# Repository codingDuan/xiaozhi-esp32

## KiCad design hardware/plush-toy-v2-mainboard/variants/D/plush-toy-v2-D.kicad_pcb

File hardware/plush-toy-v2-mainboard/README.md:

# 毛绒玩具主板二期

设计方案：[`docs/superpowers/specs/2026-10-05-plush-toy-v2-hardware-design.md`](../../docs/superpowers/specs/2026-10-05-plush-toy-v2-hardware-design.md)
实施计划：[`docs/superpowers/plans/2026-10-05-plush-toy-v2-hardware.md`](../../docs/superpowers/plans/2026-10-05-plush-toy-v2-hardware.md)
选型记录：[`SELECTION.md`](SELECTION.md)　电池防反接：[`BATTERY_PROTECTION.md`](BATTERY_PROTECTION.md)

四个版本共用一份电路描述（`scripts/v2/`），各自一份布局（`scripts/placement_<X>.py`），产物在 `variants/<X>/`。

## 命令

```sh
cd hardware/plush-toy-v2-mainboard/scripts
KP=/Applications/KiCad/KiCad.app/Contents/Frameworks/Python.framework/Versions/Current/bin/python3
python3 -m unittest test_parts_db test_gpio test_core test_variants test_netlist   # 电路描述与原理图
python3 gen_schematic.py --variant A
$KP gen_pcb.py --variant A
$KP -m unittest test_pcb_A
$KP shrink.py --variant A        # 试探能否继续缩小（不改文件）
$KP fanout.py --variant A && $KP route.py --variant A   # 扇出 + Freerouting，成功后存 build/routed-snapshot
$KP post_route.py --variant A --from-snapshot           # 网格补线（不重跑 Freerouting）
bash export_fab.sh A             # 测试 + Gerber/BOM/坐标/库存报告/渲染图 → variants/A/fab/
python3 export_wiring.py --variant A                    # 接线表与外购清单
$KP export_camera_check.py --variant C                  # C/D：1:1 摄像头实物核验稿（非生产文件）
```

## 版本状态

| 版本 | 状态 | 尺寸 |
|---|---|---|
| A 不带摄像头 · 单面 | 生产文件已出，待委托方决定是否打样 | 54×46mm |
| B 不带摄像头 · 双面 | 生产文件已出，待首板实测 | 50×46mm |
| C 带摄像头 · 单面 | 生产文件已出，待首板断电测量与实测 | 65×55mm |
| D 带摄像头 · 双面 | 生产文件已出，待首板断电测量与实测 | 65×55mm |

## 版本 A 尺寸迭代

| 轮次 | 尺寸 | 面积 / 一期 5400mm² | 结果 |
|---|---|---|---|
| 0 | 52×42 | 40% | spec 估算起点。按委托方要求加每个引脚的丝印标注后，右下角、右上角的标注与座子冲突 |
| 1 | 52×46 | 44% | 可行：全部器件与丝印放下，布局测试通过 |
| 2 | 51×46 | 43% | 失败：左上安装孔与触摸座重叠 |
| 2 | 52×45 | 43% | 失败：触摸座、测温座的引脚标注放不下 |
| 4 | 54×46 | 46% | 去耦复查后加宽 2mm（委托方 2026-10-05 同意）：去耦电容须贴引脚同侧，52×46 只剩 1 个降压位置且布不通 |

**结论**：单面版本的尺寸由板边长度决定，不由面积决定：上边 4 个、下边 4 个、右边 3 个出线座已排满，左边是模组与天线。再缩小需要减少出线座或改双面（版本 B）。
暂不加布线余量：板中部仍有空地，Task 10 布线不收敛时再加。

## 版本 A 结果（2026-10-05）

| 项 | 结果 |
|---|---|
| 尺寸 | 54×46mm，4 层，面积 2484mm²，**一期的 46%** |
| 器件 | 88 颗全部贴片（单面），BOM 38 行；另有 8 个背面测试点、2 个安装孔，**板上无手焊件** |
| 扩展库 | 20 种（每种每单一笔换料费），库存全部 ≥ 20，见 `variants/A/fab/parts_report.txt` |
| 单板器件费 | 约 $13.1（嘉立创 1–49 片档；ESP32 模组 $5.14 占四成，其次 MAX98357A $1.32、LIS2DH12 $0.93、eFuse $0.87） |
| DRC（重新灌铜后） | 0 错误、0 未连接、原理图一致性 0；孔距按错误检查。警告 17 条均为丝印：舵机排针外形伸出板边（设计如此）、模组天线外形、外框相碰、电池座自带外框压到其固定焊盘（导出时自动裁掉） |
| 布局质量（测试保证） | 去耦电容焊盘距所服务引脚 ≤ 3mm 且在同侧（第二颗储能电容 ≤ 6mm）；降压热回路表层 1.2mm；降压输出焊盘直接打孔进 3V3 平面；功率网络无长细线；出线座全部卧式、开口朝板边；功能名不会印到邻座旁 |
| 生产文件 | `variants/A/fab/`：`gerber.zip`、`bom.csv`、`positions.csv` |
| 接线 / 验收 | [`variants/A/WIRING.md`](variants/A/WIRING.md)、[`variants/A/TESTING.md`](variants/A/TESTING.md) |
| 渲染图 | `variants/A/renders/final_top.png`、`final_bottom.png` |

固件需要配套改动（另立计划）：I2C 在 GPIO43/44，LIS2DH12 地址 0x19，开机后经 I2C 关掉 IP5306 轻载关机，
按 CC 电压判定是否允许加热。

## 版本 C 结果（2026-10-05）

| 项 | 结果 |
|---|---|
| 尺寸 | 65×55mm，4 层，单面贴片 |
| 装配 | 除背面测试点和安装孔外，所有器件均为正面 SMT；所有线束座为卧式、开口朝板外，板上无手焊件 |
| 静态验收 | `test_pcb_C` 24/24，`test_drc_C` 5/5；重新灌铜后 0 DRC 错误、0 未连接、0 原理图一致性问题 |
| 摄像头安全 | J_CAM 自动检查焊盘反序映射；实物照片与一期 2 号板断电导通记录交叉确认：触点朝下、镜头朝板外、摄像头 pin 1 → PCB pad 24；首板上电前仍须通过 spec §7.4 断电测量 |
| 生产文件 | `variants/C/fab/`：`gerber.zip`、44 行 `bom.csv`、Top 107 项 `positions.csv`、库存报告；全部料号库存 ≥20 |
| 接线 / 验收 | [`variants/C/WIRING.md`](variants/C/WIRING.md)、[`variants/C/TESTING.md`](variants/C/TESTING.md)、[`variants/C/CAMERA_VERIFICATION.md`](variants/C/CAMERA_VERIFICATION.md) |
| 渲染图 | `variants/C/renders/final_top.png`、`final_bottom.png` |

## 版本 D 结果（2026-10-05）

| 项 | 结果 |
|---|---|
| 尺寸 | 65×55mm，4 层，双面贴片 |
| 装配 | 107 个工厂贴装坐标：Top 19 + Bottom 88；所有线束座为卧式、开口朝板外，板上无手焊件 |
| 静态验收 | `test_pcb_D` 26/26，`test_drc_D` 6/6；重新灌铜后 0 DRC 错误、0 未连接、0 原理图一致性问题 |
| 摄像头安全 | 与 C 相同的反序映射和实物方向证据；首板上电前仍须通过 spec §7.4 断电测量 |
| 生产文件 | `variants/D/fab/`：`gerber.zip`（含 `F.Paste`、`B.Paste`）、44 行 `bom.csv`、Top 19 + Bottom 88 项 `positions.csv`、库存报告；全部料号库存 ≥20 |
| 接线 / 验收 | [`variants/D/WIRING.md`](variants/D/WIRING.md)、[`variants/D/TESTING.md`](variants/D/TESTING.md)、[`variants/D/CAMERA_VERIFICATION.md`](variants/D/CAMERA_VERIFICATION.md) |
| 渲染图 | `variants/D/renders/final_top.png`、`final_bottom.png` |

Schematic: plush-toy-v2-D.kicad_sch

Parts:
C_ADC: 100nF; C_0402_1005Metric; LCSC C1525
C_AMP: 100nF; C_0402_1005Metric; LCSC C1525
C_AMP_BULK: 10uF; C_0603_1608Metric; LCSC C19702
C_BAT_NTC: 100nF; C_0402_1005Metric; LCSC C1525
C_BUCK_HF: 100nF; C_0402_1005Metric; LCSC C1525
C_BUCK_IN: 10uF; C_0603_1608Metric; LCSC C19702
C_BUCK_OUT1, C_BUCK_OUT2: 22uF; C_0805_2012Metric; LCSC C45783
C_CAM_AVDD: 100nF; C_0402_1005Metric; LCSC C1525
C_CAM_DVDD: 100nF; C_0402_1005Metric; LCSC C1525
C_CAM_RST: 100nF; C_0402_1005Metric; LCSC C1525
C_CC_SENSE: 10nF; C_0402_1005Metric; LCSC C15195
C_CHG_BAT: 22uF; C_0805_2012Metric; LCSC C45783
C_CHG_VIN: 22uF; C_0805_2012Metric; LCSC C45783
C_EFUSE_DVDT: 3.3nF; C_0402_1005Metric; LCSC C696855
C_EFUSE_IN: 100nF; C_0402_1005Metric; LCSC C1525
C_EN: 1uF; C_0402_1005Metric; LCSC C52923
C_FF: 22pF; C_0402_1005Metric; LCSC C1555
C_IMU: 100nF; C_0402_1005Metric; LCSC C1525
C_LCD: 100nF; C_0402_1005Metric; LCSC C1525
C_LDO15_IN, C_LDO15_OUT, C_LDO28_IN, C_LDO28_OUT: 1uF; C_0402_1005Metric; LCSC C52923
C_MIC: 100nF; C_0402_1005Metric; LCSC C1525
C_NTC: 100nF; C_0402_1005Metric; LCSC C1525
C_SERVO1, C_SERVO2, C_SERVO3: 22uF; C_0805_2012Metric; LCSC C45783
C_TOUCH: 100nF; C_0402_1005Metric; LCSC C1525
C_TOUCH_VREG: 100nF; C_0402_1005Metric; LCSC C1525
C_U1: 100nF; C_0402_1005Metric; LCSC C1525
C_U1_BULK: 10uF; C_0603_1608Metric; LCSC C19702
C_VBAT_SENSE: 100nF; C_0402_1005Metric; LCSC C1525
C_VSYS1, C_VSYS2: 22uF; C_0805_2012Metric; LCSC C45783
C_VUSB: 10uF; C_0603_1608Metric; LCSC C19702
D_ESD_MUTE: LESD8D3.3CAT5G; D_SOD-882; LCSC C172409
D_ESD_PWR: LESD8D3.3CAT5G; D_SOD-882; LCSC C172409
D_ESD_TOUCH: LESD8D3.3CAT5G; D_SOD-882; LCSC C172409
D_USB_DN: LESD8D3.3CAT5G; D_SOD-882; LCSC C172409
D_USB_DP: LESD8D3.3CAT5G; D_SOD-882; LCSC C172409
F_USB: BSMD1206-150-6V; Fuse_1206_3216Metric; LCSC C883132
H1, H2: M2; MountingHole_2.2mm_M2
J_ARM_L: SERVO 2.54-1x3P; HDR-SMD_3P-P2.54-H-M_KH-2.54PH-1X3P-L13.5-WT; LCSC C46061676
J_ARM_R: SERVO 2.54-1x3P; HDR-SMD_3P-P2.54-H-M_KH-2.54PH-1X3P-L13.5-WT; LCSC C46061676
J_BAT: BAT PH2.0; CONN-SMD_2P-P2.00_HANXIA_HX-PH2.0-2PWT; LCSC C22461285
J_CAM: AFC01-S24FCA-00; FPC-SMD_24P-P0.50_AFC01-S24FCA-00; LCSC C262669
J_HEAT: HEAT XH2.54-2P; CONN-SMD_2P-P2.54_MEGASTAR_ZX-XH2.54-2PWT; LCSC C7429671
J_KEY: KEY SH1.0-3P; CONN-SMD_3P-P1.00_MEGASTAR_ZX-SH1.0-3PWT; LCSC C7430445
J_LCD: LCD SH1.0-8P; JST_SH_SM08B-SRSS-TB_1x08-1MP_P1.00mm_Horizontal; LCSC C160407
J_MIC: MIC SH1.0-6P; CONN-SMD_HCTL_HC-1.0-6PWT; LCSC C2845365
J_NTC: SH1.0-2P; JST_SH_SM02B-SRSS-TB_1x02-1MP_P1.00mm_Horizontal; LCSC C160402
J_SPK: SH1.0-2P; JST_SH_SM02B-SRSS-TB_1x02-1MP_P1.00mm_Horizontal; LCSC C160402
J_TOUCH: SH1.0-2P; JST_SH_SM02B-SRSS-TB_1x02-1MP_P1.00mm_Horizontal; LCSC C160402
J_USB: TYPE-C-31-M-12; USB_C_Receptacle_HRO_TYPE-C-31-M-12; LCSC C165948
L_BUCK: 2.2uH; IND-SMD_L4.0-W4.0_YHNR4020; LCSC C2926400
L_CHG: 1uH; IND-SMD_L5.0-W5.0_SMNR5030; LCSC C135287
Q_BATN: AO3400A; SOT-23; LCSC C20917
Q_BATP: AO3401A; SOT-23; LCSC C15127
Q_HEAT: AO3400A; SOT-23; LCSC C20917
Q_LCD_BL: AO3401A; SOT-23; LCSC C15127
RT_BAT: 10k NTC; R_0603_1608Metric; LCSC C13564
R_AMP_SD: 1M; R_0402_1005Metric; LCSC C26083
R_BATN_G: 100k; R_0402_1005Metric; LCSC C25741
R_BATN_PD: 1M; R_0402_1005Metric; LCSC C26083
R_BATP_BYP: 10k; R_0402_1005Metric; LCSC C25744
R_BATP_PU: 1M; R_0402_1005Metric; LCSC C26083
R_BAT_NTC: 10k; R_0402_1005Metric; LCSC C25744
R_BOOT: 10k; R_0402_1005Metric; LCSC C25744
R_CAM_PWDN: 10k; R_0402_1005Metric; LCSC C25744
R_CAM_RST: 10k; R_0402_1005Metric; LCSC C25744
R_CC1, R_CC2: 5.1k; R_0402_1005Metric; LCSC C25905
R_CC_SUM1, R_CC_SUM2: 100k; R_0402_1005Metric; LCSC C25741
R_EFUSE_ILM: 1k; R_0402_1005Metric; LCSC C11702
R_EN: 10k; R_0402_1005Metric; LCSC C25744
R_FB1: 100k; R_0402_1005Metric; LCSC C25741
R_FB2: 22k; R_0402_1005Metric; LCSC C25768
R_GATE: 100; R_0402_1005Metric; LCSC C25076
R_GATE_PD: 100k; R_0402_1005Metric; LCSC C25741
R_KEY_MUTE_PU: 10k; R_0402_1005Metric; LCSC C25744
R_LCD_BL_GATE: 100; R_0402_1005Metric; LCSC C25076
R_LCD_BL_OFF: 100k; R_0402_1005Metric; LCSC C25741
R_LCD_CLK: 33; R_0402_1005Metric; LCSC C25105
R_LCD_MOSI: 33; R_0402_1005Metric; LCSC C25105
R_NTC: 10k; R_0402_1005Metric; LCSC C25744
R_SCL: 4.7k; R_0402_1005Metric; LCSC C25900
R_SDA: 4.7k; R_0402_1005Metric; LCSC C25900
R_SERVO_R_PD: 10k; R_0402_1005Metric; LCSC C25744
R_SIOC: 4.7k; R_0402_1005Metric; LCSC C25900
R_SIOD: 4.7k; R_0402_1005Metric; LCSC C25900
R_TOUCH_REXT: 75k; R_0402_1005Metric; LCSC C25798
R_VBAT_BOT: 100k; R_0402_1005Metric; LCSC C25741
R_VBAT_TOP: 100k; R_0402_1005Metric; LCSC C25741
SW_BOOT: TS-1088-AR02016; SW-SMD_L3.9-W3.0-P4.45; LCSC C720477
SW_RST: TS-1088-AR02016; SW-SMD_L3.9-W3.0-P4.45; LCSC C720477
TP_3V3: +3V3; TestPoint_Pad_D1.0mm
TP_BOOT: BOOT; TestPoint_Pad_D1.0mm
TP_CC: CC_SENSE; TestPoint_Pad_D1.0mm
TP_EN: EN; TestPoint_Pad_D1.0mm
TP_GND: GND; TestPoint_Pad_D1.0mm
TP_VBAT: VBAT; TestPoint_Pad_D1.0mm
TP_VSYS: VSYS; TestPoint_Pad_D1.0mm
TP_VUSB: VUSB; TestPoint_Pad_D1.0mm
U1: ESP32-S3-WROOM-1-N16R8; ESP32-S3-WROOM-1; LCSC C2913202
U_ADC: ADS1115IDGSR; TSSOP-10_3x3mm_P0.5mm; LCSC C37593
U_AMP: MAX98357AETE+T; TQFN-16-1EP_3x3mm_P0.5mm_EP1.23x1.23mm; LCSC C910544
U_BUCK: SY8089AAAC; SOT-23-5; LCSC C78988
U_CHG: IP5306-I2C; ESOP-8_L4.9-W3.9-P1.27-LS6.0-BL-EP2.0; LCSC C488349
U_EFUSE: TPS259531DSGR; Texas_DSG0008A_WSON-8-1EP_2x2mm_P0.5mm_EP0.9x1.6mm_ThermalV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; LCSC C2155674
U_IMU: LIS2DH12TR; LGA-12_L2.0-W2.0-P0.50-BL; LCSC C110926
U_LDO15: ME6211C15M5G-N; SOT-23-5; LCSC C53100
U_LDO28: ME6211C28M5G-N; SOT-23-5; LCSC C53099
U_TOUCH: MPR121QR2; UQFN-20_3x3mm_P0.4mm; LCSC C91322

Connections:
+1V5: C_CAM_DVDD.1, C_LDO15_OUT.1, J_CAM.15, U_LDO15.5 (V_{OUT})
+2V8: C_CAM_AVDD.1, C_LDO28_OUT.1, J_CAM.14, J_CAM.21, R_CAM_RST.1, R_SIOC.2, R_SIOD.2, U_LDO28.5 (V_{OUT})
+3V3: C_ADC.1, C_BUCK_OUT1.1, C_BUCK_OUT2.1, C_FF.1, C_IMU.1, C_LCD.1, C_LDO15_IN.1, C_LDO28_IN.1, C_MIC.1, C_TOUCH.1, C_U1.1, C_U1_BULK.1, J_LCD.7, J_MIC.1, L_BUCK.2, Q_LCD_BL.2 (S), R_BAT_NTC.1, R_BOOT.1, R_EN.1, R_FB1.1, R_KEY_MUTE_PU.1, R_LCD_BL_OFF.1, R_NTC.1, R_SCL.2, R_SDA.2, TP_3V3.1, U1.2 (3V3), U_ADC.8 (VDD), U_IMU.2 (CS), U_IMU.3 (SDO/SA0), U_IMU.9 (VDD), U_IMU.10 (VDD_IO), U_LDO15.1 (V_{IN}), U_LDO15.3 (CE), U_LDO28.1 (V_{IN}), U_LDO28.3 (CE), U_TOUCH.20 (VDD)
AMP_BCLK: U1.33 (IO40), U_AMP.16 (BCLK)
AMP_DIN: U1.32 (IO39), U_AMP.1 (DIN)
AMP_LRCLK: U1.34 (IO41), U_AMP.14 (LRCLK)
AMP_SD: R_AMP_SD.2, U_AMP.4 (~SD_MODE)
BATN_GATE: Q_BATN.1 (G), R_BATN_G.2, R_BATN_PD.1
BATP_GATE: Q_BATN.3 (D), Q_BATP.1 (G), R_BATP_PU.2
BAT_NTC_SENSE: C_BAT_NTC.1, RT_BAT.1, R_BAT_NTC.2, U_ADC.7 (AIN3)
BOOT: R_BOOT.2, SW_BOOT.1, TP_BOOT.1, U1.27 (IO0)
BUCK_FB: C_FF.2, R_FB1.2, R_FB2.1, U_BUCK.5 (FB)
BUCK_SW: L_BUCK.1, U_BUCK.3 (SW)
CAM_HREF: J_CAM.16, U1.7 (IO7)
CAM_PCLK: J_CAM.8, U1.21 (IO13)
CAM_PWDN: J_CAM.17, R_CAM_PWDN.1
CAM_RESET: C_CAM_RST.1, J_CAM.19, R_CAM_RST.2
CAM_SIOC: J_CAM.20, R_SIOC.1, U1.5 (IO5)
CAM_SIOD: J_CAM.22, R_SIOD.1, U1.4 (IO4)
CAM_VSYNC: J_CAM.18, U1.6 (IO6)
CAM_XCLK: J_CAM.12, U1.8 (IO15)
CAM_Y2: J_CAM.6, U1.19 (IO11)
CAM_Y3: J_CAM.4, U1.17 (IO9)
CAM_Y4: J_CAM.3, U1.12 (IO8)
CAM_Y5: J_CAM.5, U1.18 (IO10)
CAM_Y6: J_CAM.7, U1.20 (IO12)
CAM_Y7: J_CAM.9, U1.11 (IO18)
CAM_Y8: J_CAM.11, U1.10 (IO17)
CAM_Y9: J_CAM.13, U1.9 (IO16)
CC1: J_USB.A5 (CC1), R_CC1.1, R_CC_SUM1.1
CC2: J_USB.B5 (CC2), R_CC2.1, R_CC_SUM2.1
CC_SENSE: C_CC_SENSE.1, R_CC_SUM1.2, R_CC_SUM2.2, TP_CC.1, U_ADC.6 (AIN2)
CHG_SW: L_CHG.1, U_CHG.7 (SW)
EFUSE_DVDT: C_EFUSE_DVDT.1, U_EFUSE.1 (dVdt)
EFUSE_ILM: R_EFUSE_ILM.1, U_EFUSE.7 (ILM)
EN: C_EN.1, R_EN.2, SW_RST.1, TP_EN.1, U1.3 (EN)
GND: C_ADC.2, C_AMP.2, C_AMP_BULK.2, C_BAT_NTC.2, C_BUCK_HF.2, C_BUCK_IN.2, C_BUCK_OUT1.2, C_BUCK_OUT2.2, C_CAM_AVDD.2, C_CAM_DVDD.2, C_CAM_RST.2, C_CC_SENSE.2, C_CHG_BAT.2, C_CHG_VIN.2, C_EFUSE_DVDT.2, C_EFUSE_IN.2, C_EN.2, C_IMU.2, C_LCD.2, C_LDO15_IN.2, C_LDO15_OUT.2, C_LDO28_IN.2, C_LDO28_OUT.2, C_MIC.2, C_NTC.2, C_SERVO1.2, C_SERVO2.2, C_SERVO3.2, C_TOUCH.2, C_TOUCH_VREG.2, C_U1.2, C_U1_BULK.2, C_VBAT_SENSE.2, C_VSYS1.2, C_VSYS2.2, C_VUSB.2, D_ESD_MUTE.2 (A2), D_ESD_PWR.2 (A2), D_ESD_TOUCH.2 (A2), D_USB_DN.2 (A2), D_USB_DP.2 (A2), J_ARM_L.3, J_ARM_R.3, J_BAT.2, J_CAM.10, J_CAM.23, J_CAM.25, J_CAM.26, J_KEY.3, J_LCD.6, J_MIC.2, J_MIC.6, J_NTC.2, J_TOUCH.2, J_USB.A1 (GND), J_USB.A12 (GND), J_USB.B1 (GND), J_USB.B12 (GND), J_USB.SH (SHIELD), Q_BATN.2 (S), Q_HEAT.2 (S), RT_BAT.2, R_BATN_PD.2, R_CAM_PWDN.2, R_CC1.2, R_CC2.2, R_EFUSE_ILM.2, R_FB2.2, R_GATE_PD.2, R_SERVO_R_PD.2, R_TOUCH_REXT.2, R_VBAT_BOT.2, SW_BOOT.2, SW_RST.2, TP_GND.1, U1.1 (GND), U1.40 (GND), U1.41 (GND), U_ADC.1 (ADDR), U_ADC.3 (GND), U_AMP.3 (GND), U_AMP.11 (GND), U_AMP.15 (GND), U_AMP.17 (PAD), U_BUCK.2 (GND), U_CHG.9 (EP), U_EFUSE.8 (GND), U_EFUSE.9 (EP), U_IMU.5 (RES), U_IMU.6 (GND), U_IMU.7 (GND), U_IMU.8 (GND), U_LDO15.2 (V_{SS}), U_LDO28.2 (V_{SS}), U_TOUCH.4 (ADDR), U_TOUCH.6 (VSS)
HEAT_GATE: Q_HEAT.1 (G), R_GATE.2, R_GATE_PD.1
HEAT_GATE_DRV: R_GATE.1, U_TOUCH.12 (LED0/ELE4)
HEAT_LOW: J_HEAT.2, Q_HEAT.3 (D)
I2C_SCL: R_SCL.1, U1.37 (TXD0), U_ADC.10 (SCL), U_CHG.2 (LED1), U_IMU.1 (SCL/SPC), U_TOUCH.2 (SCL)
I2C_SDA: R_SDA.1, U1.36 (RXD0), U_ADC.9 (SDA), U_CHG.3 (LED2), U_IMU.4 (SDA/SDI/SDO), U_TOUCH.3 (SDA)
KEY_MUTE: D_ESD_MUTE.1 (A1), J_KEY.2, R_KEY_MUTE_PU.2, U_TOUCH.13 (LED1/ELE5)
KEY_PWR: D_ESD_PWR.1 (A1), J_KEY.1, U_CHG.5 (KEY)
LCD_BL: J_LCD.8, Q_LCD_BL.3 (D)
LCD_BL_GATE: Q_LCD_BL.1 (G), R_LCD_BL_GATE.2, R_LCD_BL_OFF.2
LCD_BL_PWM: R_LCD_BL_GATE.1, U1.25 (IO48)
LCD_CLK: R_LCD_CLK.1, U1.31 (IO38)
LCD_CLK_S: J_LCD.5, R_LCD_CLK.2
LCD_CS: J_LCD.2, U1.26 (IO45)
LCD_DC: J_LCD.3, U1.24 (IO47)
LCD_MOSI: R_LCD_MOSI.1, U1.22 (IO14)
LCD_MOSI_S: J_LCD.4, R_LCD_MOSI.2
LCD_RST: J_LCD.1, U1.23 (IO21)
MIC_SCK: J_MIC.5, U1.38 (IO2)
MIC_SD: J_MIC.3, U1.35 (IO42)
MIC_WS: J_MIC.4, U1.39 (IO1)
NTC_SENSE: C_NTC.1, J_NTC.1, R_NTC.2, U_ADC.4 (AIN0)
SERVO_L_PWM: J_ARM_L.1, U1.15 (IO3)
SERVO_R_PWM: J_ARM_R.1, R_SERVO_R_PD.1, U1.16 (IO46)
SPK_N: J_SPK.2, U_AMP.10 (OUTN)
SPK_P: J_SPK.1, U_AMP.9 (OUTP)
TOUCH_E0: D_ESD_TOUCH.1 (A1), J_TOUCH.1, U_TOUCH.8 (ELE0)
TOUCH_REXT: R_TOUCH_REXT.1, U_TOUCH.7 (REXT)
TOUCH_VREG: C_TOUCH_VREG.1, U_TOUCH.5 (VREG)
USB_DN: D_USB_DN.1 (A1), J_USB.A7 (D-), J_USB.B7 (D-), U1.13 (USB_D-)
USB_DP: D_USB_DP.1 (A1), J_USB.A6 (D+), J_USB.B6 (D+), U1.14 (USB_D+)
VBAT: C_CHG_BAT.1, L_CHG.2, Q_BATP.2 (S), R_BATP_BYP.1, R_BATP_PU.1, R_VBAT_TOP.1, TP_VBAT.1, U_CHG.6 (BAT)
VBAT_PACK: J_BAT.1, Q_BATP.3 (D), R_BATN_G.1, R_BATP_BYP.2
VBAT_SENSE: C_VBAT_SENSE.1, R_VBAT_BOT.1, R_VBAT_TOP.2, U_ADC.5 (AIN1)
VBUS_FUSED: C_EFUSE_IN.1, F_USB.2, U_EFUSE.2 (EN/UVLO), U_EFUSE.3 (IN), U_EFUSE.4 (IN)
VBUS_IN: F_USB.1, J_USB.A4 (VBUS), J_USB.A9 (VBUS), J_USB.B4 (VBUS), J_USB.B9 (VBUS)
VSYS: C_AMP.1, C_AMP_BULK.1, C_BUCK_HF.1, C_BUCK_IN.1, C_SERVO1.1, C_SERVO2.1, C_SERVO3.1, C_VSYS1.1, C_VSYS2.1, J_ARM_L.2, J_ARM_R.2, R_AMP_SD.1, TP_VSYS.1, U_AMP.7 (VDD), U_AMP.8 (VDD), U_BUCK.1 (EN), U_BUCK.4 (VIN), U_CHG.8 (VOUT)
VUSB: C_CHG_VIN.1, C_VUSB.1, J_HEAT.1, TP_VUSB.1, U_CHG.1 (VIN), U_EFUSE.5 (OUT)

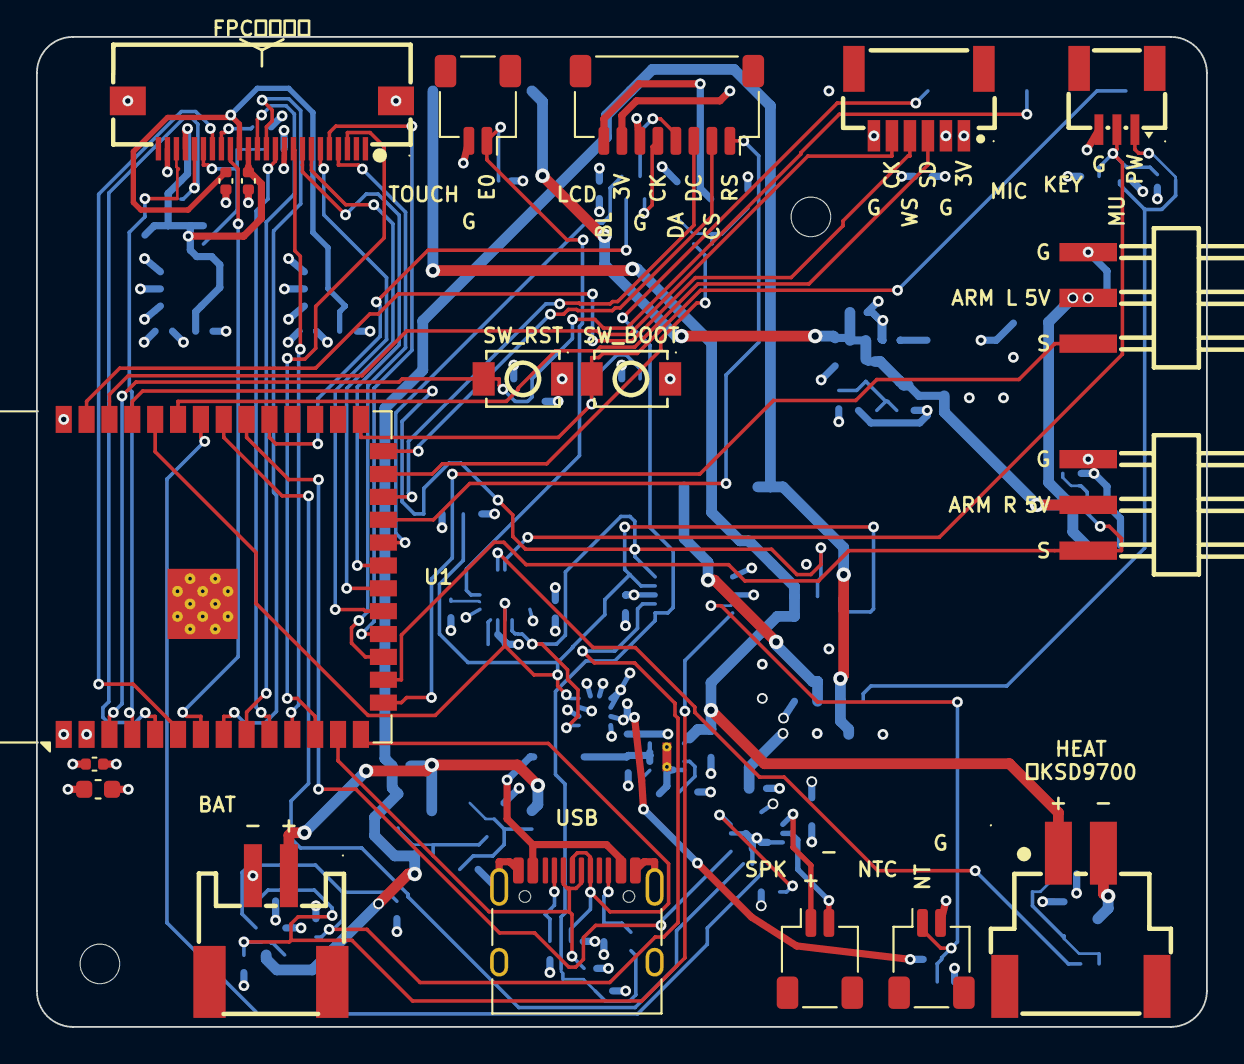
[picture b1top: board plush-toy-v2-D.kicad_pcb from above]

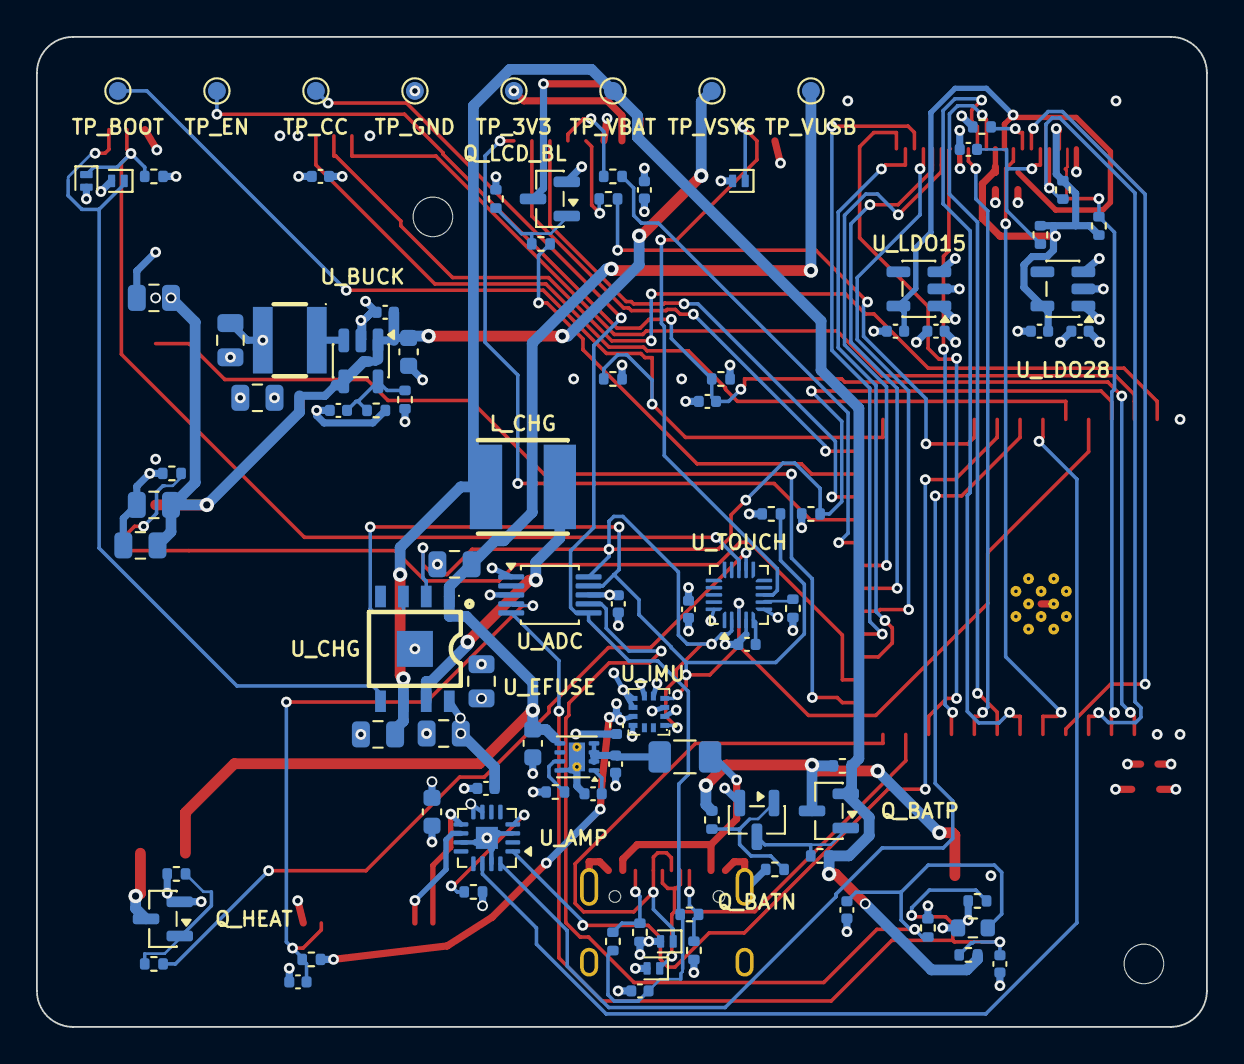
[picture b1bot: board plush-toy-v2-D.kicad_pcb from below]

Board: 4 copper layers, 65.0 x 55.0 mm, 117 parts (96 on the bottom side), 74 nets.

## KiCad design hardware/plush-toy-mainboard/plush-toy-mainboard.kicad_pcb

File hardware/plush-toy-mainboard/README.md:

# plush-toy 主板（4 层）

设计依据：[`docs/superpowers/specs/2026-09-14-plush-toy-pcb-4layer-design.md`](../../docs/superpowers/specs/2026-09-14-plush-toy-pcb-4layer-design.md)。引脚以 [`main/boards/plush-toy/config.h`](../../main/boards/plush-toy/config.h) 为唯一事实来源，本工程不得改动任何 GPIO 分配。

## 状态

| 阶段 | 状态 | 产物 |
|---|---|---|
| 工具链 | 完成 | KiCad 10.0.6、OpenJDK 26（Freerouting 2.4.1 需 Java 25+） |
| 器件与连接数据 | 完成 | USB eFuse、必贴 SCCB 上拉、头部触摸连接器与 3.3V 状态灯已加入 |
| 原理图 | 完成 | ERC、网表往返与 PCB 原理图一致性检查通过 |
| 布局 | 完成 | 降压、ESP32 去耦/EN 与 XCLK 关键几何均由测试锁定 |
| 走线 | 完成 | 0 条未连接；内层保持纯电源平面；仅余 2 个已审阅 U1 丝印告警 |
| 制造文件 | 完成 | Gerber/BOM/CPL 已从最终 PCB 重新导出并通过静态检查 |
| 首板验收 | 清单完成，待打样 | [`TESTING.md`](TESTING.md)：制造文件、电源隔离、接口、外设、热与压力测试 |

## 已定的物理约束

- 板子 **90×60mm，单面贴片**（原定 70×50mm 按实际封装量放不下）
- 摄像头为 **OV3660**（排线丝印 TY-OV3660-21MM-V3.0），金手指朝下插入，用下接触 FPC 座
- 圆屏 7 针顺序、舵机线序均已对照实物确认

## 原理图评审需要委托方确认的三件事（已全部确认，2026-09-14）

1. **摄像头排线金手指朝向**：拍一张 OV2640 排线末端的照片。本板按下接触 FPC 座（AFC01-S24FCA-00）绘制，若金手指朝上需换上接触座（设计方案 12.5 节）。
2. **两块圆屏的 7 针顺序**：拍屏幕模块排针丝印，确认是 RST / CS / DC / SDA / SCL / GND / VCC。
3. **舵机插头顺序**：本板按 PWM / V+ / GND，与原 PCA9685 模块一致；若舵机线序不同需调换。

## 布线流水线

重新布线按顺序执行（均用 KiCad 自带 Python，记作 `KP`）：

```sh
cd hardware/plush-toy-mainboard/scripts
KP=/Applications/KiCad/KiCad.app/Contents/Frameworks/Python.framework/Versions/Current/bin/python3
$KP gen_pcb.py                                                     # 外框、放置、铺铜、丝印
$KP fanout.py                                                      # 电源平面、密脚距器件与相机 FPC 的确定性扇出
JAVA_TOOL_OPTIONS=-Djava.awt.headless=true $KP route.py 30          # Freerouting 自动布线，约 5 分钟
$KP post_route.py --apply                                          # 候选板完整 DRC/一致性通过后才覆盖正式 PCB
$KP -m unittest test_pcb test_drc -v                               # 布局、DRC、未连接与原理图一致性
```

**当前正式 PCB 的来历（2026-09-14 第二轮评审修改）**：以提交 c7b9cb5 已收敛的布线为起点，运行 `$KP apply_review_eco.py && $KP post_route.py --apply` 做三项局部修改（5V/触摸丝印挪位、C_BUCK_IN 转 180°、VBUS_FUSED 0.5mm 主干），其余走线未动。同样的意图已写进 `placement.py` 与 `fanout.py`，但**从 `gen_pcb.py` 整板重跑目前不收敛**：连续两轮 Freerouting + 收尾都在 U_TOUCH / J_CAM 密集区留下 6 条开路（TOUCH_E1/E4/E5/E6、CAM_VSYNC、CAM_HREF）。下次需要整板重布时先解决这一区域的确定性出线。

**已知坑**（都已写进脚本与测试）：
- 独立脚本里 `board.Save()` 会把 KiCad 默认规则写回 `.kicad_pro`，冲掉网络类。每次保存后必须 `project_rules.apply()`，否则 DRC 按默认 0.2mm 间距报几百处假错误
- 内层 In1 / In2 必须设为 power 类型，否则 Freerouting 会把信号线走在 GND / 3V3 平面上
- Freerouting 不会主动打过孔接平面，所以先跑 `fanout.py`
- Freerouting 的收尾结果不稳定；`route.py` 会拒绝未连接增加、新 DRC error 或一致性缺陷替换，并在运行前删除旧 SES；`post_route.py` 每次都从正式 PCB 生成独立候选，不自动续用来源不明的旧候选，完整检查后才允许 `--apply`
- 相机 0.5mm FPC、IMU、触摸与功放先做确定性逃逸；最终收尾会删除已被正式路径替代的悬空 stub/过孔，并按网络类宽度重走超过 2mm 的窄电源线
- 收尾路由器的窄颈逃逸会在宽焊盘出口留下 0.2mm 短线，逐段 2mm 的检查抓不到。保险丝到 eFuse 的 VBUS_FUSED 主干因此在 `fanout.py` 按 0.5mm 预布并锁定；`test_high_current_nets_have_no_long_necks` 把 VBUS/VMOT/PGND 等主干上相连的窄线合并计长，只允许在比线宽还窄的焊盘出口处总长 ≤ 2mm
- U1 标准库封装的天线边界丝印距板边约 0.54mm，不涉及铜、阻焊或铣刀路径；工程保留 warning，并由测试按告警类型、对象和坐标精确白名单，避免掩盖新增问题
- 描述性位号（如 `C_ADC`）不符合 KiCad 自动注释的字母+数字格式，制造 BOM 必须由 `board_spec.py` 经 `export_bom.py` 导出，不能直接使用 KiCad BOM 导出器
- 生成过程中请勿在 KiCad 图形界面里保存 PCB，会覆盖脚本结果

**2026-09-14 静态验收结果**：

| 检查 | 结果 | 处理 |
|---|---|---|
| KiCad DRC | 0 错误、2 个已审阅告警 | U1 标准封装天线端两条丝印线距板边约 0.54mm；告警按对象精确白名单，未全局屏蔽；其余孔间距、铜间距、板边与禁布区规则均通过 |
| 未连接项 | 0 | DRC 驱动的候选补线通过后应用 |
| 原理图一致性 | 通过 | `--schematic-parity` 与逐网络测试均通过 |
| 板级结构与 DRC | 通过 | 包含电源线宽/过孔、连接器/IC 丝印、PGND 锚线、完整 DRC 与原理图一致性 |
| 制造文件 | 通过 | BOM 与坐标各 81 个唯一自动贴装位号，均有 LCSC 料号且无 `?`；9 个接线座手焊；Gerber zip 14 个文件、无空文件 |
| 实物电气与信号质量 | 待首板 | 按 [`TESTING.md`](TESTING.md) 验证 USB、DVP、SPI、音频、供电与热测试 |

## 运行测试

```sh
cd hardware/plush-toy-mainboard/scripts
python3 -m unittest test_kicad_env test_config_pins test_board_spec test_part_pins test_netlist_roundtrip test_export_bom -v
/Applications/KiCad/KiCad.app/Contents/Frameworks/Python.framework/Versions/Current/bin/python3 -m unittest test_project_lib -v
/Applications/KiCad/KiCad.app/Contents/Frameworks/Python.framework/Versions/Current/bin/python3 -m unittest test_pcb test_drc test_post_route -v
```

静态检查通过后，按 [`TESTING.md`](TESTING.md) 完成下单前检查；收到首板后继续填写分域上电、接口、外设、热和压力测试的实测记录。

## 已知设计错误

- **J_CAM 引脚顺序反了**（2026-10-05 确认）：摄像头第 k 脚落在板上第 25−k 脚，接上即短路 +1V5，#1 因此损坏。**不要直接接摄像头**，详见 `TESTING.md` 事故记录。本板已生产，不改 `board_spec.py`；二期修正。

## 已知风险

DRC 通过只证明连接与规则正确。天线、40MHz SPI、摄像头 DVP、USB 90Ω 的实际质量只能打样验证，第一版预计需要改版。详见设计方案第 10 节。

## 目录约定

```
plush-toy-mainboard.kicad_pro   工程
plush-toy-mainboard.kicad_sch   原理图（按功能分页）
plush-toy-mainboard.kicad_pcb   PCB
lib/                            工程专用符号与封装（KiCad 官方库没有的）
scripts/                        生成与检查脚本，含 config.h 引脚对照检查
fab/                            制造文件，下单直接用这个目录
renders/                        各阶段渲染图
```

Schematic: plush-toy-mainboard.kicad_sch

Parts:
C_ADC: 100nF; C_0402_1005Metric; LCSC C1525
C_AMP: 100nF; C_0402_1005Metric; LCSC C1525
C_AMP_BULK: 10uF; C_0603_1608Metric; LCSC C19702
C_BUCK_HF: 100nF; C_0402_1005Metric; LCSC C1525
C_BUCK_IN: 22uF; C_0805_2012Metric; LCSC C45783
C_BUCK_OUT1, C_BUCK_OUT2: 22uF; C_0805_2012Metric; LCSC C45783
C_CAM_AVDD: 100nF; C_0402_1005Metric; LCSC C1525
C_CAM_DVDD: 100nF; C_0402_1005Metric; LCSC C1525
C_CAM_RST: 100nF; C_0402_1005Metric; LCSC C1525
C_EFUSE_DVDT: 3.3nF; C_0402_1005Metric; LCSC C696855
C_EFUSE_IN: 100nF; C_0402_1005Metric; LCSC C1525
C_EN: 1uF; C_0402_1005Metric; LCSC C52923
C_FF: 22pF; C_0402_1005Metric; LCSC C1555
C_IMU: 100nF; C_0402_1005Metric; LCSC C1525
C_IMU_CP: 2.2nF; C_0402_1005Metric; LCSC C1531
C_IMU_REG: 100nF; C_0402_1005Metric; LCSC C1525
C_IMU_VLOGIC: 10nF; C_0402_1005Metric; LCSC C15195
C_LCD: 100nF; C_0402_1005Metric; LCSC C1525
C_LDO15_IN, C_LDO15_OUT, C_LDO28_IN, C_LDO28_OUT: 1uF; C_0402_1005Metric; LCSC C52923
C_NTC: 100nF; C_0402_1005Metric; LCSC C1525
C_PWM: 100nF; C_0402_1005Metric; LCSC C1525
C_TOUCH: 100nF; C_0402_1005Metric; LCSC C1525
C_TOUCH_VREG: 100nF; C_0402_1005Metric; LCSC C1525
C_U1: 100nF; C_0402_1005Metric; LCSC C1525
C_U1_BULK: 10uF; C_0603_1608Metric; LCSC C19702
C_VMOT_BULK: 1000uF 10V; CAP-SMD_BD10.0-L10.3-W10.3-LS11.3-FD; LCSC C970713
C_VMOT_HF: 100nF; C_0402_1005Metric; LCSC C1525
D_USB_DN: LESD8D3.3CAT5G; D_SOD-882; LCSC C172409
D_USB_DP: LESD8D3.3CAT5G; D_SOD-882; LCSC C172409
D_VMOT_TVS: SMBJ5.0A; D_SMB; LCSC C129528
F_USB: BSMD1206-150-6V; Fuse_1206_3216Metric; LCSC C883132
H1, H2, H3, H4: M3; MountingHole_3.2mm_M3
J_CAM: AFC01-S24FCA-00; FPC-SMD_24P-P0.50_AFC01-S24FCA-00; LCSC C262669
J_EXT: Debug / Keys; JST_SH_BM05B-SRSS-TB_1x05-1MP_P1.00mm_Vertical; LCSC C160391
J_HEAT: Heater; JST_VH_B2P-VH_1x02_P3.96mm_Vertical
J_LCD_L: LCD L; PinHeader_1x08_P2.54mm_Vertical
J_LCD_R: LCD R; PinHeader_1x08_P2.54mm_Vertical
J_MIC: Mic; JST_SH_BM06B-SRSS-TB_1x06-1MP_P1.00mm_Vertical; LCSC C160392
J_NTC: NTC 10K; JST_PH_B2B-PH-K_1x02_P2.00mm_Vertical
J_SERVO_L: Servo L; PinHeader_1x03_P2.54mm_Vertical
J_SERVO_R: Servo R; PinHeader_1x03_P2.54mm_Vertical
J_SPK: Speaker; JST_PH_B2B-PH-K_1x02_P2.00mm_Vertical
J_TOUCH: Head Touch; JST_PH_B2B-PH-K_1x02_P2.00mm_Vertical
J_USB: TYPE-C-31-M-12; USB_C_Receptacle_HRO_TYPE-C-31-M-12; LCSC C165948
J_VMOT: VMOT 5V; TerminalBlock_CUI_TB007-508-02_1x02_P5.08mm_Horizontal
L_BUCK: 2.2uH; IND-SMD_L4.0-W4.0_YHNR4020; LCSC C2926400
Q_HEAT: AO3400A; SOT-23; LCSC C20917
Q_LCD_BL: AO3401A; SOT-23; LCSC C15127
Q_REV: AO3401A; SOT-23; LCSC C15127
R_AMP_SD: 1M; R_0402_1005Metric; LCSC C26083
R_BOOT: 10k; R_0402_1005Metric; LCSC C25744
R_BUCK_EN: 100k; R_0402_1005Metric; LCSC C25741
R_CAM_PWDN: 10k; R_0402_1005Metric; LCSC C25744
R_CAM_RST: 10k; R_0402_1005Metric; LCSC C25744
R_CC1, R_CC2: 5.1k; R_0402_1005Metric; LCSC C25905
R_EFUSE_ILM: 1k; R_0402_1005Metric; LCSC C11702
R_EN: 10k; R_0402_1005Metric; LCSC C25744
R_FB1: 100k; R_0402_1005Metric; LCSC C25741
R_FB2: 22k; R_0402_1005Metric; LCSC C25768
R_GATE: 100; R_0402_1005Metric; LCSC C25076
R_GATE_PD: 100k; R_0402_1005Metric; LCSC C25741
R_LCD_BL_GATE: 100; R_0402_1005Metric; LCSC C25076
R_LCD_BL_OFF: 100k; R_0402_1005Metric; LCSC C25741
R_LCD_CLK: 33; R_0402_1005Metric; LCSC C25105
R_LCD_MOSI: 33; R_0402_1005Metric; LCSC C25105
R_NTC: 10k; R_0402_1005Metric; LCSC C25744
R_OE: 10k; R_0402_1005Metric; LCSC C25744
R_REV: 10k; R_0402_1005Metric; LCSC C25744
R_SCL: 4.7k; R_0402_1005Metric; LCSC C25900
R_SDA: 4.7k; R_0402_1005Metric; LCSC C25900
R_SIOC: 4.7k; R_0402_1005Metric; LCSC C25900
R_SIOD: 4.7k; R_0402_1005Metric; LCSC C25900
R_STAR: 0; R_0402_1005Metric; LCSC C17168
R_TOUCH_REXT: 75k; R_0402_1005Metric; LCSC C25798
SW_BOOT: TS-1187A-B-A-B; SW-SMD_4P-L5.1-W5.1-P3.70-LS6.5-TL_H1.5; LCSC C318884
SW_RST: TS-1187A-B-A-B; SW-SMD_4P-L5.1-W5.1-P3.70-LS6.5-TL_H1.5; LCSC C318884
TP_3V3: +3V3; TestPoint_Pad_D1.0mm
TP_E1: TOUCH_E1; TestPoint_Pad_D1.0mm
TP_E2: TOUCH_E2; TestPoint_Pad_D1.0mm
TP_E3: TOUCH_E3; TestPoint_Pad_D1.0mm
TP_E4: TOUCH_E4; TestPoint_Pad_D1.0mm
TP_E5: TOUCH_E5; TestPoint_Pad_D1.0mm
TP_E6: TOUCH_E6; TestPoint_Pad_D1.0mm
TP_E7: TOUCH_E7; TestPoint_Pad_D1.0mm
TP_E8: TOUCH_E8; TestPoint_Pad_D1.0mm
TP_E9: TOUCH_E9; TestPoint_Pad_D1.0mm
TP_E10: TOUCH_E10; TestPoint_Pad_D1.0mm
TP_E11: TOUCH_E11; TestPoint_Pad_D1.0mm
TP_GATE: HEAT_GATE; TestPoint_Pad_D1.0mm
TP_GND: GND; TestPoint_Pad_D1.0mm
TP_OE: PWM_OE; TestPoint_Pad_D1.0mm
TP_PGND: PGND; TestPoint_Pad_D1.0mm
TP_SCL: I2C_SCL; TestPoint_Pad_D1.0mm
TP_SDA: I2C_SDA; TestPoint_Pad_D1.0mm
TP_TX: UART_TX; TestPoint_Pad_D1.0mm
TP_VBUS: VBUS; TestPoint_Pad_D1.0mm
TP_VMOT: VMOT; TestPoint_Pad_D1.0mm
U1: ESP32-S3-WROOM-1-N16R8; ESP32-S3-WROOM-1; LCSC C2913202
U_ADC: ADS1115IDGSR; TSSOP-10_3x3mm_P0.5mm; LCSC C37593
U_AMP: MAX98357AETE+T; TQFN-16-1EP_3x3mm_P0.5mm_EP1.23x1.23mm; LCSC C910544
U_BUCK: SY8089AAAC; SOT-23-5; LCSC C78988
U_EFUSE: TPS259531DSGR; Texas_DSG0008A_WSON-8-1EP_2x2mm_P0.5mm_EP0.9x1.6mm_ThermalV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; LCSC C2155674
U_IMU: MPU-6050; InvenSense_QFN-24_4x4mm_P0.5mm; LCSC C24112
U_LDO15: ME6211C15M5G-N; SOT-23-5; LCSC C53100
U_LDO28: ME6211C28M5G-N; SOT-23-5; LCSC C53099
U_PWM: PCA9685PW; TSSOP-28_4.4x9.7mm_P0.65mm; LCSC C2678753
U_TOUCH: MPR121QR2; UQFN-20_3x3mm_P0.4mm; LCSC C91322

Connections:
+1V5: C_CAM_DVDD.1, C_LDO15_OUT.1, J_CAM.10, U_LDO15.5 (V_{OUT})
+2V8: C_CAM_AVDD.1, C_LDO28_OUT.1, J_CAM.4, J_CAM.11, R_CAM_RST.1, R_SIOC.2, R_SIOD.2, U_LDO28.5 (V_{OUT})
+3V3: C_ADC.1, C_BUCK_OUT1.1, C_BUCK_OUT2.1, C_FF.1, C_IMU.1, C_IMU_VLOGIC.1, C_LCD.1, C_LDO15_IN.1, C_LDO28_IN.1, C_PWM.1, C_TOUCH.1, C_U1.1, C_U1_BULK.1, J_EXT.1, J_LCD_L.7, J_LCD_R.7, J_MIC.1, L_BUCK.2, Q_LCD_BL.2 (S), R_BOOT.1, R_EN.1, R_FB1.1, R_LCD_BL_OFF.1, R_NTC.1, R_SCL.2, R_SDA.2, TP_3V3.1, U1.2 (3V3), U_ADC.8 (VDD), U_IMU.8 (VLOGIC), U_IMU.13 (VDD), U_LDO15.1 (V_{IN}), U_LDO15.3 (CE), U_LDO28.1 (V_{IN}), U_LDO28.3 (CE), U_PWM.28 (VDD), U_TOUCH.20 (VDD)
AMP_BCLK: U1.33 (IO40), U_AMP.16 (BCLK)
AMP_DIN: U1.32 (IO39), U_AMP.1 (DIN)
AMP_LRCLK: U1.34 (IO41), U_AMP.14 (LRCLK)
AMP_SD: R_AMP_SD.2, U_AMP.4 (~SD_MODE)
BOOT: J_EXT.4, R_BOOT.2, SW_BOOT.1 (A), SW_BOOT.2 (B), U1.27 (IO0)
BUCK_EN: R_BUCK_EN.2, U_BUCK.1 (EN)
BUCK_FB: C_FF.2, R_FB1.2, R_FB2.1, U_BUCK.5 (FB)
BUCK_SW: L_BUCK.1, U_BUCK.3 (SW)
CAM_HREF: J_CAM.9, U1.7 (IO7)
CAM_PCLK: J_CAM.17, U1.21 (IO13)
CAM_PWDN: J_CAM.8, R_CAM_PWDN.1
CAM_RESET: C_CAM_RST.1, J_CAM.6, R_CAM_RST.2
CAM_SIOC: J_CAM.5, R_SIOC.1, U1.5 (IO5)
CAM_SIOD: J_CAM.3, R_SIOD.1, U1.4 (IO4)
CAM_VSYNC: J_CAM.7, U1.6 (IO6)
CAM_XCLK: J_CAM.13, U1.8 (IO15)
CAM_Y2: J_CAM.19, U1.19 (IO11)
CAM_Y3: J_CAM.21, U1.17 (IO9)
CAM_Y4: J_CAM.22, U1.12 (IO8)
CAM_Y5: J_CAM.20, U1.18 (IO10)
CAM_Y6: J_CAM.18, U1.20 (IO12)
CAM_Y7: J_CAM.16, U1.11 (IO18)
CAM_Y8: J_CAM.14, U1.10 (IO17)
CAM_Y9: J_CAM.12, U1.9 (IO16)
EFUSE_DVDT: C_EFUSE_DVDT.1, U_EFUSE.1 (dVdt)
EFUSE_ILM: R_EFUSE_ILM.1, U_EFUSE.7 (ILM)
EN: C_EN.1, J_EXT.3, R_EN.2, SW_RST.1 (A), SW_RST.2 (B), U1.3 (EN)
GND: C_ADC.2, C_AMP.2, C_AMP_BULK.2, C_BUCK_HF.2, C_BUCK_IN.2, C_BUCK_OUT1.2, C_BUCK_OUT2.2, C_CAM_AVDD.2, C_CAM_DVDD.2, C_CAM_RST.2, C_EFUSE_DVDT.2, C_EFUSE_IN.2, C_EN.2, C_IMU.2, C_IMU_CP.2, C_IMU_REG.2, C_IMU_VLOGIC.2, C_LCD.2, C_LDO15_IN.2, C_LDO15_OUT.2, C_LDO28_IN.2, C_LDO28_OUT.2, C_NTC.2, C_PWM.2, C_TOUCH.2, C_TOUCH_VREG.2, C_U1.2, C_U1_BULK.2, D_USB_DN.2 (A2), D_USB_DP.2 (A2), J_CAM.2, J_CAM.15, J_CAM.25, J_CAM.26, J_EXT.5, J_LCD_L.6, J_LCD_R.6, J_MIC.2, J_MIC.6, J_NTC.2, J_TOUCH.2, J_USB.A1 (GND), J_USB.A12 (GND), J_USB.B1 (GND), J_USB.B12 (GND), J_USB.SH (SHIELD), R_CAM_PWDN.2, R_CC1.2, R_CC2.2, R_EFUSE_ILM.2, R_FB2.2, R_OE.2, R_STAR.2, R_TOUCH_REXT.2, SW_BOOT.3 (C), SW_BOOT.4 (D), SW_RST.3 (C), SW_RST.4 (D), TP_GND.1, U1.1 (GND), U1.40 (GND), U1.41 (GND), U_ADC.1 (ADDR), U_ADC.3 (GND), U_AMP.3 (GND), U_AMP.11 (GND), U_AMP.15 (GND), U_AMP.17 (PAD), U_BUCK.2 (GND), U_EFUSE.8 (GND), U_EFUSE.9 (EP), U_IMU.1 (CLKIN), U_IMU.9 (AD0), U_IMU.11 (FSYNC), U_IMU.18 (GND), U_LDO15.2 (V_{SS}), U_LDO28.2 (V_{SS}), U_PWM.1 (A0), U_PWM.2 (A1), U_PWM.3 (A2), U_PWM.4 (A3), U_PWM.5 (A4), U_PWM.14 (VSS), U_PWM.24 (A5), U_PWM.25 (EXTCLK), U_TOUCH.4 (ADDR), U_TOUCH.6 (VSS)
HEAT_GATE: Q_HEAT.1 (G), R_GATE.2, R_GATE_PD.1, TP_GATE.1
HEAT_LOW: J_HEAT.2, Q_HEAT.3 (D)
HEAT_PWM: R_GATE.1, U_PWM.22 (LED15)
I2C_SCL: R_SCL.1, TP_SCL.1, U1.15 (IO3), U_ADC.10 (SCL), U_IMU.23 (SCL), U_PWM.26 (SCL), U_TOUCH.2 (SCL)
I2C_SDA: R_SDA.1, TP_SDA.1, U1.36 (RXD0), U_ADC.9 (SDA), U_IMU.24 (SDA), U_PWM.27 (SDA), U_TOUCH.3 (SDA)
IMU_CPOUT: C_IMU_CP.1, U_IMU.20 (CPOUT)
IMU_REGOUT: C_IMU_REG.1, U_IMU.10 (REGOUT)
LCD_BL: J_LCD_L.8, J_LCD_R.8, Q_LCD_BL.3 (D)
LCD_BL_GATE: Q_LCD_BL.1 (G), R_LCD_BL_GATE.2, R_LCD_BL_OFF.2
LCD_BL_PWM: R_LCD_BL_GATE.1, U1.25 (IO48)
LCD_CLK: R_LCD_CLK.1, U1.31 (IO38)
LCD_CLK_S: J_LCD_L.5, J_LCD_R.5, R_LCD_CLK.2
LCD_CS_L: J_LCD_L.2, U1.26 (IO45)
LCD_CS_R: J_LCD_R.2, U1.16 (IO46)
LCD_DC: J_LCD_L.3, J_LCD_R.3, U1.24 (IO47)
LCD_MOSI: R_LCD_MOSI.1, U1.22 (IO14)
LCD_MOSI_S: J_LCD_L.4, J_LCD_R.4, R_LCD_MOSI.2
LCD_RST: J_LCD_L.1, J_LCD_R.1, U1.23 (IO21)
MIC_SCK: J_MIC.5, U1.38 (IO2)
MIC_SD: J_MIC.3, U1.35 (IO42)
MIC_WS: J_MIC.4, U1.39 (IO1)
NTC_SENSE: C_NTC.1, J_NTC.1, R_NTC.2, U_ADC.4 (AIN0)
PGND: C_VMOT_BULK.2, C_VMOT_HF.2, D_VMOT_TVS.2 (A), J_SERVO_L.3, J_SERVO_R.3, J_VMOT.2, Q_HEAT.2 (S), R_GATE_PD.2, R_REV.2, R_STAR.1, TP_PGND.1
PWM_OE: R_OE.1, TP_OE.1, U_PWM.23 (~OE)
REV_GATE: Q_REV.1 (G), R_REV.1
SERVO_L_PWM: J_SERVO_L.1, U_PWM.6 (LED0)
SERVO_R_PWM: J_SERVO_R.1, U_PWM.7 (LED1)
SPK_N: J_SPK.2, U_AMP.10 (OUTN)
SPK_P: J_SPK.1, U_AMP.9 (OUTP)
TOUCH_E0: J_TOUCH.1, U_TOUCH.8 (ELE0)
TOUCH_E1: TP_E1.1, U_TOUCH.9 (ELE1)
TOUCH_E2: TP_E2.1, U_TOUCH.10 (ELE2)
TOUCH_E3: TP_E3.1, U_TOUCH.11 (ELE3)
TOUCH_E4: TP_E4.1, U_TOUCH.12 (LED0/ELE4)
TOUCH_E5: TP_E5.1, U_TOUCH.13 (LED1/ELE5)
TOUCH_E6: TP_E6.1, U_TOUCH.14 (LED2/ELE6)
TOUCH_E7: TP_E7.1, U_TOUCH.15 (LED3/ELE7)
TOUCH_E8: TP_E8.1, U_TOUCH.16 (LED4/ELE8)
TOUCH_E9: TP_E9.1, U_TOUCH.17 (LED5/ELE9)
TOUCH_E10: TP_E10.1, U_TOUCH.18 (LED6/ELE10)
TOUCH_E11: TP_E11.1, U_TOUCH.19 (LED7/ELE11)
TOUCH_REXT: R_TOUCH_REXT.1, U_TOUCH.7 (REXT)
TOUCH_VREG: C_TOUCH_VREG.1, U_TOUCH.5 (VREG)
UART_TX: J_EXT.2, TP_TX.1, U1.37 (TXD0)
USB_CC1: J_USB.A5 (CC1), R_CC1.1
USB_CC2: J_USB.B5 (CC2), R_CC2.1
USB_DN: D_USB_DN.1 (A1), J_USB.A7 (D-), J_USB.B7 (D-), U1.13 (USB_D-)
USB_DP: D_USB_DP.1 (A1), J_USB.A6 (D+), J_USB.B6 (D+), U1.14 (USB_D+)
VBUS: C_AMP.1, C_AMP_BULK.1, C_BUCK_HF.1, C_BUCK_IN.1, R_AMP_SD.1, R_BUCK_EN.1, TP_VBUS.1, U_AMP.7 (VDD), U_AMP.8 (VDD), U_BUCK.4 (VIN), U_EFUSE.5 (OUT)
VBUS_FUSED: C_EFUSE_IN.1, F_USB.2, U_EFUSE.2 (EN/UVLO), U_EFUSE.3 (IN), U_EFUSE.4 (IN)
VBUS_IN: F_USB.1, J_USB.A4 (VBUS), J_USB.A9 (VBUS), J_USB.B4 (VBUS), J_USB.B9 (VBUS)
VMOT: C_VMOT_BULK.1, C_VMOT_HF.1, D_VMOT_TVS.1 (K), J_HEAT.1, J_SERVO_L.2, J_SERVO_R.2, Q_REV.2 (S), TP_VMOT.1
VMOT_IN: J_VMOT.1, Q_REV.3 (D)

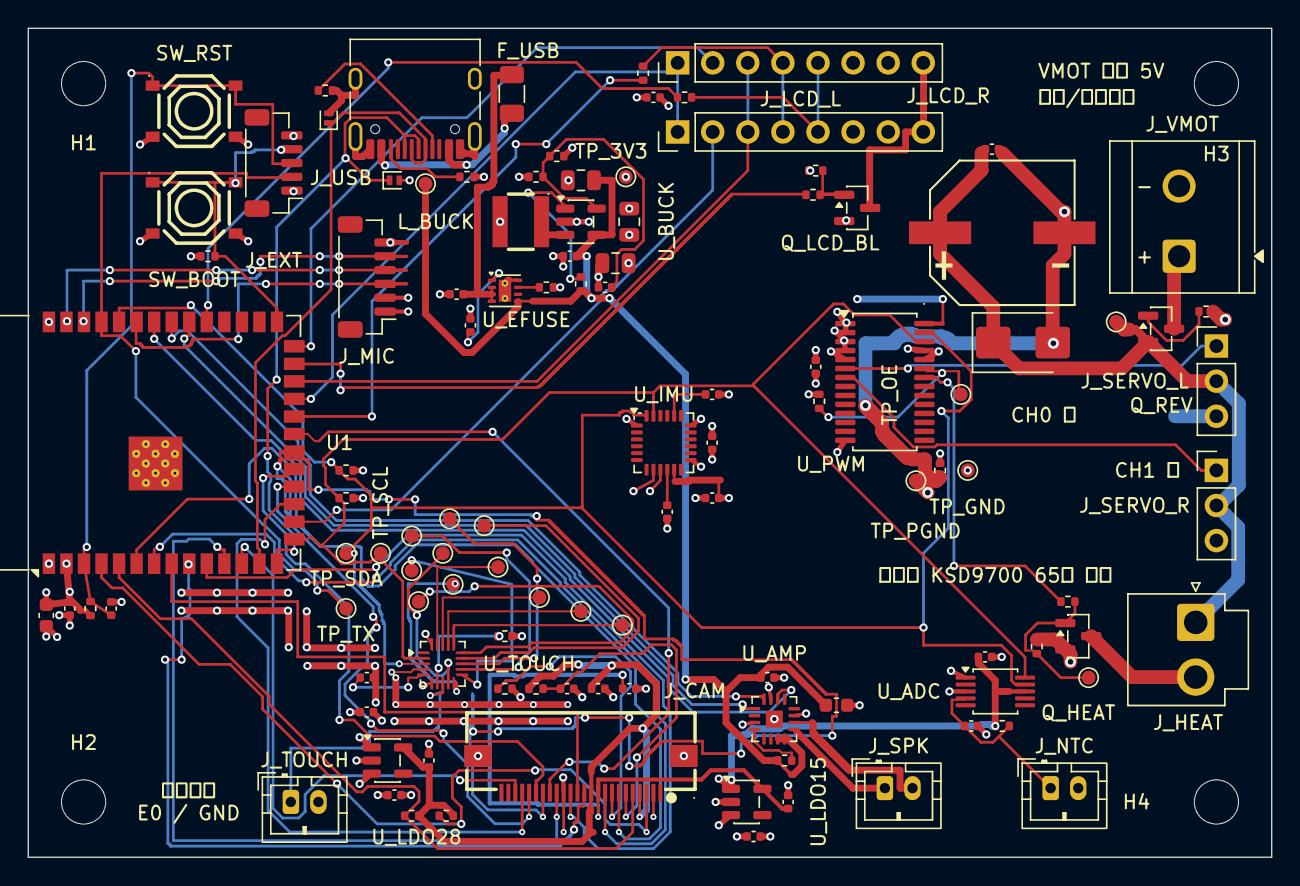
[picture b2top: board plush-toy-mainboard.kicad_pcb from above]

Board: 4 copper layers, 90.0 x 60.0 mm, 115 parts (0 on the bottom side), 84 nets.
